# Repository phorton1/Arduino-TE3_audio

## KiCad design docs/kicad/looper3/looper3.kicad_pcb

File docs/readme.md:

# TE3_audio - the teensy 4.0 based USB Audio device

This repo, based on a teensy 4.0, essentially implements a USB Audio
device that plugs into a (router to the) iPad.

It takes a 1/4" mono Guitar Audio Input, split into stereo LINE_IN
inputs (as my guitar has an active preamp that delivers sufficient
output to drive line level inputs), sends that Guitar Audio via USB
Audio to the iPad where it is processed through effects (ToneStack)
and mixed with a software based synthesizer (SampleTank), and returned
via USB Audio, which is then forwarded via I2S for processing by the
rPi Looper, and returned, once again, via I2S for final output to a
pair of stereo LINE_OUT  connectors.

It uses the SGTL5000 teensy audioShield converting the Line Inputs
into I2S data which the teensy then sends out via USB Audio to
the iPad.  It receives the returned USB Audio from the iPad and
converts it back into I2S to then send it to the Looper.  It,
finally, receives the I2S from the Looper and gives to the SGTL5000
to convert into analog Line Outputs.
processing.

It communicates with the central TE3 device vis Serial MIDI. It can
send its debugging output either to the USB Serial Device (for limited
benchtop testing) or via the Serial port to the TE3 which then forwards
it to my laptop for display.

The SGTL5000 and a software Mixer can be configured, controlled, and
polled via Serial Midi.

## Initial Implementation Notes

## Please also see

[**TE3**](https://github.com/phorton1/Arduino-TE3)
The parent **Foot Pedal** and central repositor houses and interfaces
with this device.

[**TE3_common**](https://github.com/phorton1/Arduino-libraries/TE3_commo)
Functionality and definitions common to the **TE3** and **TE3_audio** programs.

The [**circle-Looper**](https://github.com/phorton1/circle-prh-apps-Looper)
repo contains the source code for the **rPi Looper** application that runs
on a Raspberry Pi that is interfaced to this device.

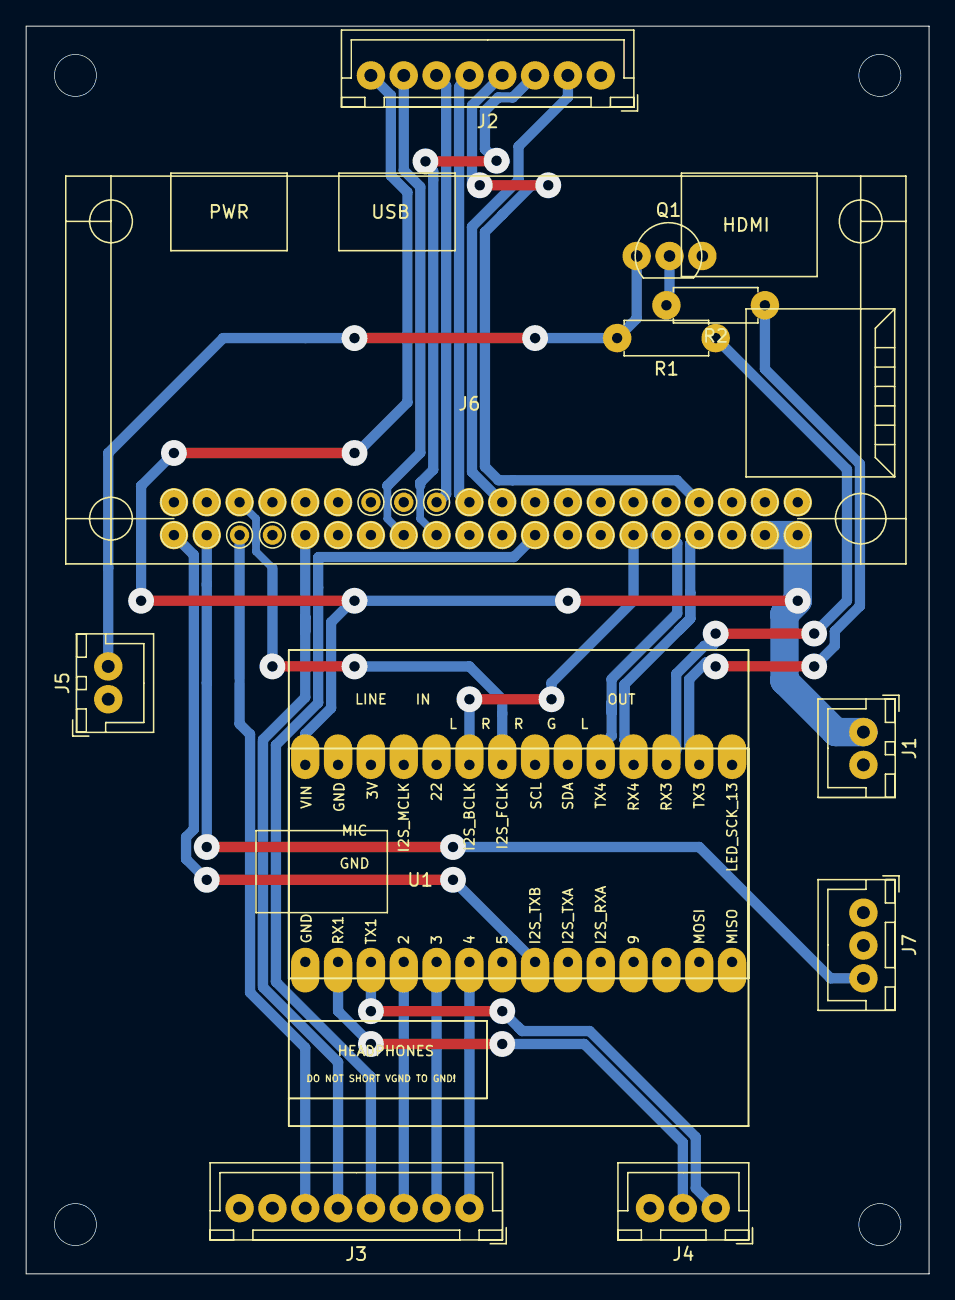
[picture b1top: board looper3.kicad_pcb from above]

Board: 2 copper layers, 69.8 x 96.5 mm, 11 parts (0 on the bottom side), 26 nets.

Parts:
J1: rPi_5V; myJSTx02
J2: RPI_DISPLAY; myJSTx08
J3: EXT_LEDS; myJSTx08
J4: TE3 SERIAL; myJSTx03
J5: RPI_RUN; myJSTx02
J6: rpi_connector; rpi_zero_2w
J7: I2S_TXB; myJSTx03
Q1: BC547; myTransistor
R1: 220; myResistor
R2: 1K; myResistor
U1: teensyAudioRevD; revDTeensy4Stack

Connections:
+5V: J1.1, J2.8, J6.2, J6.4, U1.28
GND: J1.2, J2.1, J3.7, J4.3, J5.1, J6.6, J6.9, J6.14, J6.20, J6.25, J6.30, J6.34, J6.39, Q1.3, U1.1, U1.27
I2S_BCLK: J6.12, U1.23
I2S_FCLK: J6.35, U1.22
I2S_RXB: J6.40, U1.8
I2S_TXB: J6.38, J7.3
LED_AUDIO_BUSY: J3.3, U1.4
LED_RPI_BUSY: J3.4, J6.18
LED_RPI_I2S_RX: J3.5, J6.32
LED_RPI_I2S_TX: J3.6, J6.36
LED_RPI_READY: J3.2, U1.5
LED_RPI_RUN: J3.1, U1.6
unnamed: Q1.2, R2.2
PI_REBOOT: R2.1, U1.16
RPI_LCD_CS: J2.3, J6.24
RPI_LCD_DC: J2.4, J6.7
RPI_MISO: J2.5, J6.21
RPI_MOSI: J2.2, J6.19
RPI_RUN: J5.2, Q1.1, R1.2
RPI_SCLK: J2.6, J6.23
RPI_T_CS: J2.7, J6.26
SENS_PI_RUN: R1.1, U1.17
T40_RX1: J4.2, U1.2
T40_RX4: J6.8, U1.18
T40_TX1: J4.1, U1.3
T40_TX4: J6.10, U1.19

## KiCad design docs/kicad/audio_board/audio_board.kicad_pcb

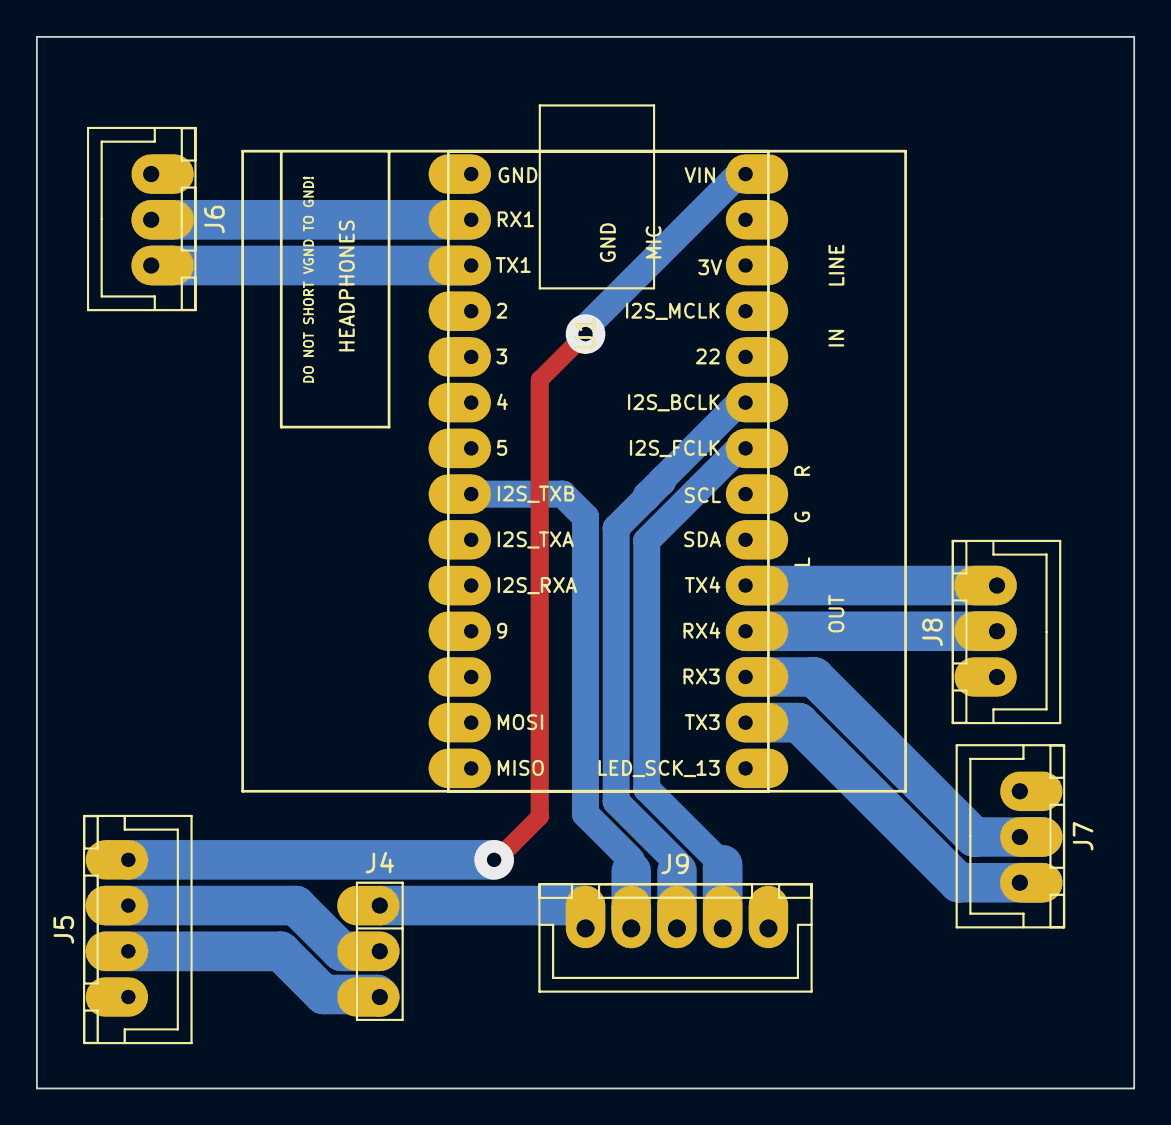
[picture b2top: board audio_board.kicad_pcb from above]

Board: 2 copper layers, 61.0 x 58.4 mm, 7 parts (0 on the bottom side), 14 nets.

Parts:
J4: T4 bottom; pinHeader1x3
J5: Host USB; JST4
J6: T4 Serial1; JST3
J7: T4 Serial3; JST3
J8: T4 Serial4; JST3
J9: rPi I2S; JST5
U1: teensyAudioRevD; audioShieldRevD

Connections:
GND: J5.1, J6.1, J7.1, J8.1, J9.5, U1.1, U1.27
HOST_D+: J4.3, J5.2
HOST_D-: J4.2, J5.3
I2S_BCLK: J9.3, U1.23
I2S_FCLK: J9.4, U1.22
T40_I2S_RXB: J4.1, J9.1
T40_I2S_TXB: J9.2, U1.8
T40_RX1: J6.2, U1.2
T40_RX3: J7.2, U1.17
T40_RX4: J8.2, U1.18
T40_TX1: J6.3, U1.3
T40_TX3: J7.3, U1.16
T40_TX4: J8.3, U1.19
T40_VIN: J5.4, U1.28

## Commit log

2024-05-11 added .gitignore to all TE related doc/kicad folders. Renamed and moved kicad designs around. See /junk/maybe_save for remnants
2024-05-12 updated kicad .gitignore's
2024-05-13 update all TE preferences.txt to build in /src/ArduinoBuilds for easier clean builds
2024-05-13 added audio_breadboard, touched the audio_board design
2024-05-13 started TE3_hub - tested midiHost and hookup to ESP32 TE3
2024-05-14 moved TE3 and TE3_hub implementation files to /src
2024-05-14 denormalized sgtl5000.h and cpp to my project (with comments)
2024-05-14 reworked API and renamed to mySGTL5000
2024-05-15 added Arduino-libraries-TE3_common repo, starting with (renamed) teSGTL5000.h and cpp
2024-05-16 initial teMIDI.h - finish (almost all of) SGTL5000 uint8_t UI in prep for MIDI API
2024-05-16 added getters to SGTL5000, implemented basic CC API, did first basic audio tests, review of default values, etc
2024-05-18 HOST mode generates a lot of noise. USB device names working with limitations, FTP Spoof worked and revealed that HOST mode generates a lot of noise.
2024-05-19 restructure and cleanup
2024-05-19 added SGTL_CC_DUMP to allow client to see all parameters
2024-05-19 added USB volume control to basic WITH_USB_AUDIO setup
2024-05-20 comments only
2024-05-20 completely reworked TE3_hub audio_system usage, #defines, and routing
2024-05-21 After first tests with iPad USB - reworked TE3_hub audio setup; reworked SGTL5000 setDefaults() and some method semantics; moved sgtl5000 implementation to TE3_hub; made sgtl5000midi.h and teCommon.h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
2024-05-22 ABANDONING TE3_hub - unfortunately, during testing several factors rule this approach out - the SGTL5000 I2S<->audio works ok and may still be in future designs, but ... - there were noticable and re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
2024-05-28 comment only
2024-05-29 added (yet another) teensyExpression2 _prototype1 kicad design for esp32-rpi-sgtl5000 testing
2024-05-31 changed USB type to simplest Audio + Single MIDI
2024-05-31 rework/cleanup TE3_HUB - added a sine wave generator for USB glitch/hiccup testing
2024-06-10 turn off USB debugging
2024-07-02 update ebay data
2025-01-22 restart TE3 project - BEFORE CHANGING TE3 TO TEENSY 4.1 - LAST ESP32 TE3 version
2025-01-23 TE3 & TE_HUB - add/cleanup USB descdriptors; move midiHost from TE_HUB to TE3
2025-01-23 IT WORKS on the iPad with AudioBus & Tonestack!!!! Yay!
2025-01-23 remove TE3_hub conditional audio defines (WITH_MIXER and WITH_SINE); remove SINE generator and inputs; adjust default SGTL5000 lineout_level for performance
2025-01-23 got rid of (many) vestigial TE3 design attempts; consolidating electronics under TE3/docs/kicad
2025-01-24 got rid of obsolete docs in prep for TE3 actual design
2025-01-24 added comments regardin I2S pin usage on teensies, audio shield(s), and rPi
2025-01-24 renamed TE3_hub to TE3_audio
2025-01-24 fixed erroneous comment re teensy4 I2S_RXB pin
2025-01-30 call setUSBSerialNumber() from _usb.c and show it in INO programs (with addl comments)
2025-01-31 update teensy Arduino preferences.txt to work on USBC hub
2025-02-02 add BUSY (as well as current ALIVE) LEDa
2025-02-02 continuing work on TE3 kicad designs
2025-02-06 changed PIN_LED_AUDIO_BUSY to prevent conflict with CS pin
2025-02-06 FINALLY landed on the store bought USBC hub solution. It works in any cable orientation and charges the iPad at 15V/25W while also working with USB midi, and presumably audio, data. - remove glue and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
2025-02-07 mod TE3 pins accoring to mother_board design (reworked breadboard)
2025-03-06 final integration test before adding audio connectors, hot gluing wires, and cutting wood base - tested with usbC hub, deleted all COM and TE3 related devices so TE3 is now COM3 and TE3_audio is COM4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
2025-03-10 added DEBUG_AUDIO_LEVELS, MONO_GUITAR_INPUT, and TEST_RPI_WITHOUT_IPAD defines - DEBUG_AUDIO_LEVELS introduces 8 AudioAnalyzePeak devices that output every 250ms or so, various levels to help me debu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
2025-03-10 had to change preferences.txt to compile while testing audio.
2025-03-10 Added audio_bug.md file as I work through problems with initial TE3 audio testing.
2025-03-11 check in TE3, TE3_audo, circle/_prh, and _apps/Looper after initial TE3 integration success. - rotaries don't work - only very few USBC cables work on the iPad, but strangely those that do, also work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
2025-03-13 IMPLEMENTED INITIAL TE3 MIDI_MONITOR; VERFIED ROTARIES NOW WORK - moved msgUnion from TE3 midiQueue.h to TE_Common/teMIDI.h - eliminated MIDI_CABLE stuff and got TE3_audio working with that change - 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
